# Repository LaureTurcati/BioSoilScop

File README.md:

# BioSoilScop
The VerY cool Cam Trap for soil ORganisms (VYCTOR)

This camera trap was designed to study ground fauna without disturbing or killing it.

VYCTOR consists of a waterproof sensor measuring approximately 25x25cm with removable and interchangeable 10cm feet. It is capable of taking images day and night thanks to a brightness detection device that activates a night vision mode with 8 infrared LEDs surrounding the camera. The system is controlled by a Raspberry Pi. The camera films continuously at low resolution (without recording) and an algorithm detects movement by comparing images in pairs (background subtraction + speed calculation + shape detection). When movement is detected, a series of high-definition photos is taken at regular intervals and stored. The device is powered by mains electricity or battery. A computer interface allows the measurement settings to be configured and the characteristics of the installation site to be entered. It has been designed to be easy to use by non-specialists.

<ins>Picture of the VYCTOR device </ins>  

 ## Examples of pictures taken
Here are some images taken during a laboratory test session.

<ins>Taken picture of a snail after motion detection</ins>

<ins>Motion detection representation</ins>

<ins>Speed detection representation</ins>

## Construction
Browse the hardware folder to construct your VYCTOR

## Documentation
Recover the documentation user and developpement in the Folder Software

## Credit
This project was funded by the French national research agency (ANR) BISES ANR-19-CE 32-0012, the OSU OREME and the OSU Ecce Terra

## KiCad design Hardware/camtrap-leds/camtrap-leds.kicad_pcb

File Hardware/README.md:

# CamTrap Hardware

Le CamTrap est organisé autour d'un Raspberry Pi.  
Il contient des parties imprimées en 3D et découpé au laser, cependant il est possible de faire sans.

## logiciels utilisés

Les PCBs ont été réalisés avec Kicad 7.0.
Les tracés laser avec Inkscape.

## Liste du Matériel

La liste du matériel se trouve dans le fichier "camtrap_bom.xlsx".

## Schéma de connection

## Liste des dossiers

Hardware  
├── camtrap/    
├── camtrap_usb_adapteur/  
├── camtrap3d/  
├── images/  
└── camtrap-leds/  

- **`camtrap`** : Contient les fichiers de fabrication de la carte head au dessus du Raspberry.  
- **`camtrap_usb_adapteur`** : Contient les fichiers de fabrication de la petite carte d'adaptation de la prise USB.  
- **`camtrap3d`** : Contient les fichiers d'impression et de découpe.  
- **`images`** : Contient les images pour le readme.  
- **`camtrap-leds`** :  Contient les fichiers de fabrication de la carte qui tient les leds

## Vue globale

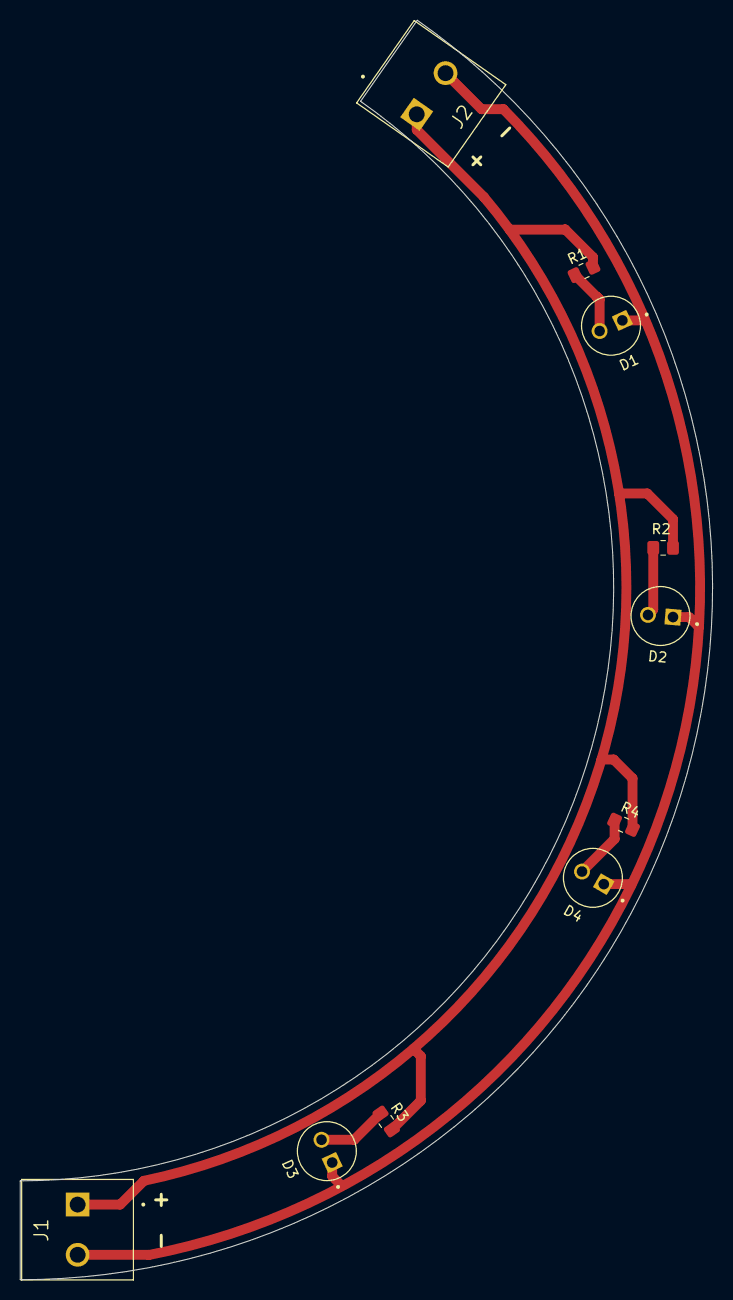
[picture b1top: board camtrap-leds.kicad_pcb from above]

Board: 2 copper layers, 70.0 x 127.3 mm, 10 parts (0 on the bottom side), 6 nets.

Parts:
D1, D2, D3, D4: TSHG6400; LEDRD254W55D595H900
J1, J2: TB010-508-02BE; CUI_TB010-508-02BE
R1, R2, R3, R4: R; R_0805_2012Metric_Pad1.20x1.40mm_HandSolder

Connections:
GND: D1.C, D2.C, D3.C, D4.C, J1.2, J2.2
unnamed: D1.A, R1.1
unnamed: D2.A, R2.1
unnamed: D3.A, R3.1
unnamed: D4.A, R4.1
unnamed: J1.1, J2.1, R1.2, R2.2, R3.2, R4.2

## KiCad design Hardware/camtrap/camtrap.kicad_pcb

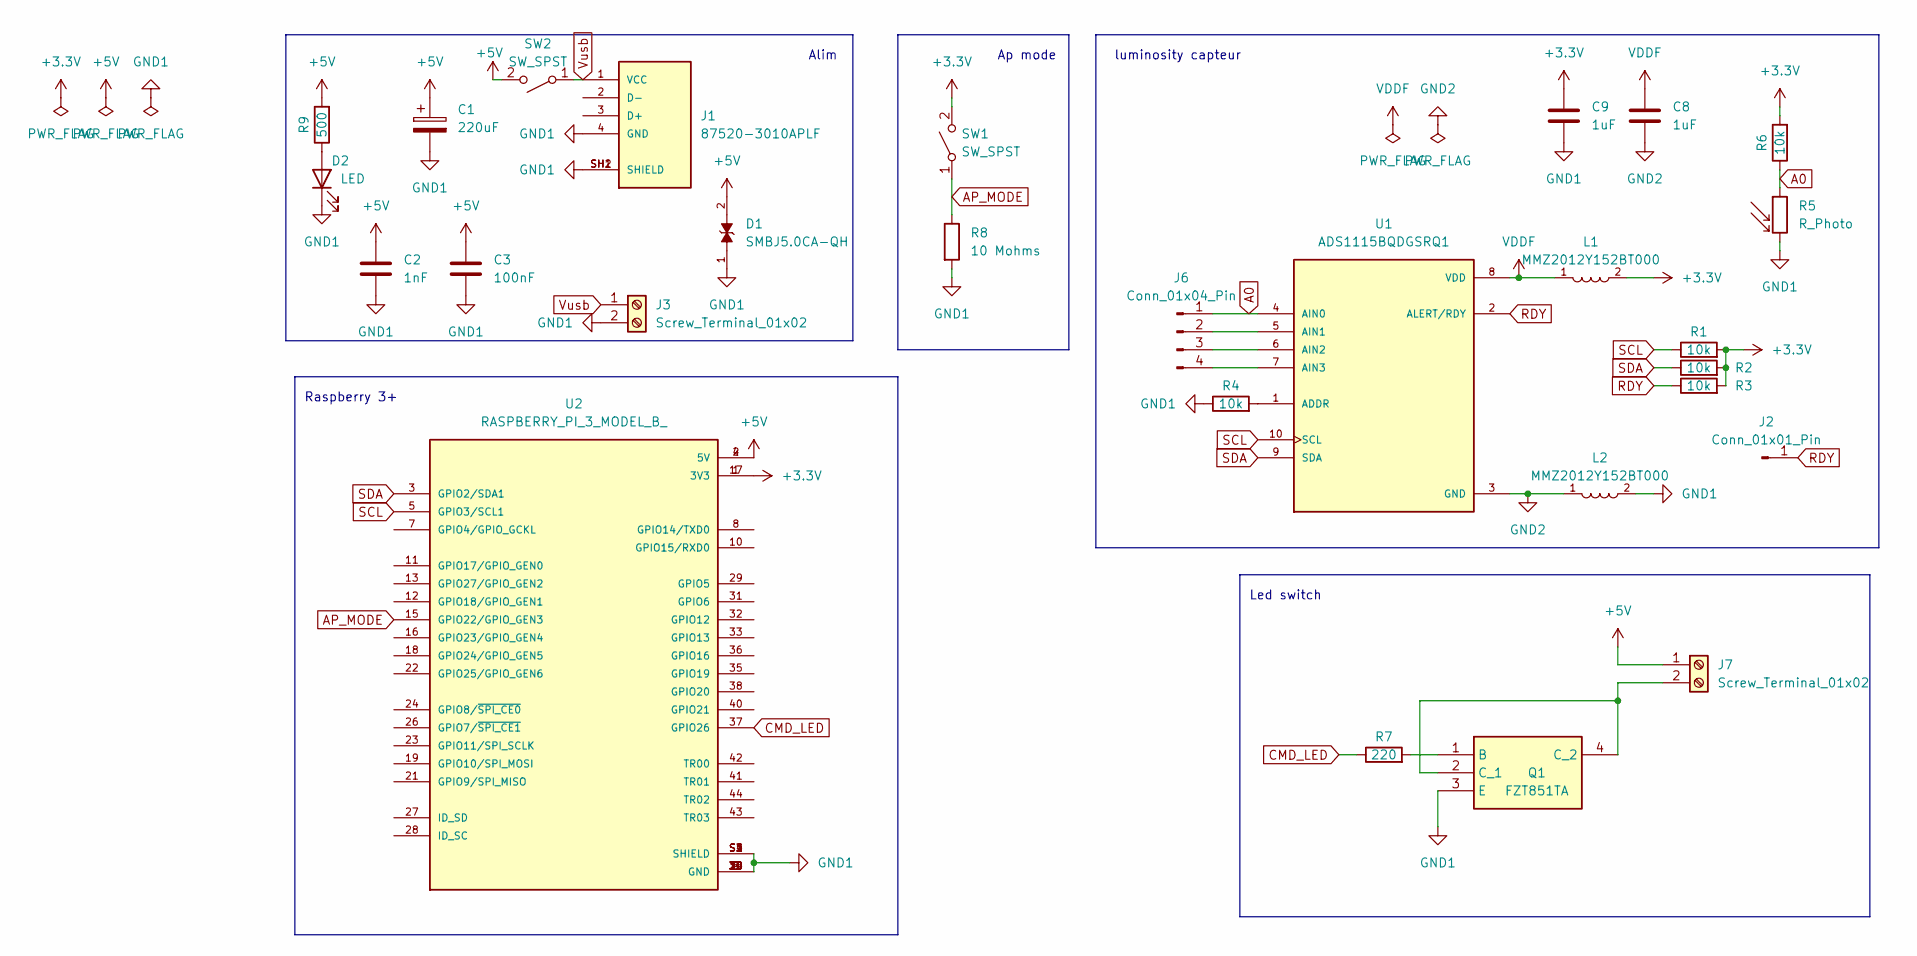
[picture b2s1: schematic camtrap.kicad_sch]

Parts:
C1: 220uF; CP_Radial_D8.0mm_P3.50mm
C2: 1nF; C_0805_2012Metric_Pad1.18x1.45mm_HandSolder
C3: 100nF; C_0805_2012Metric_Pad1.18x1.45mm_HandSolder
C8, C9: 1uF; C_0805_2012Metric_Pad1.18x1.45mm_HandSolder
D1: SMBJ5.0CA-QH; DIOM4336X265N; PARTREV I2102
D2: LED; PinHeader_1x02_P2.54mm_Vertical
J1: 87520-3010APLF; AMPHENOL_87520-3010APLF; PARTREV AR
J2: Conn_01x01_Pin; PinHeader_1x01_P2.54mm_Vertical
J3, J7: Screw_Terminal_01x02; bornierVis
J6: Conn_01x04_Pin; PinHeader_1x04_P2.54mm_Vertical
L1, L2: MMZ2012Y152BT000; INDC2012X87N
Q1: FZT851TA; SOT230P700X170-4N; Mouser Part Number 522-FZT851TA
R1, R2, R3, R4, R6: 10k; R_0805_2012Metric_Pad1.20x1.40mm_HandSolder
R5: R_Photo; PinHeader_1x02_P2.54mm_Vertical
R7: 220; R_0805_2012Metric_Pad1.20x1.40mm_HandSolder
R8: 10 Mohms; R_0805_2012Metric_Pad1.20x1.40mm_HandSolder
R9: 500; R_0805_2012Metric_Pad1.20x1.40mm_HandSolder
SW1, SW2: SW_SPST; PinHeader_1x02_P2.54mm_Vertical
U1: ADS1115BQDGSRQ1; SOP50P490X110-10N; PARTREV D
U2: RASPBERRY_PI_3_MODEL_B_; raspberrypi 3b+; PARTREV N/A

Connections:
+3.3V: C9.1, L1.2, R1.2, R2.2, R3.2, R6.2, SW1.2 (B), U2.1 (3V3), U2.17 (3V3)
+5V: C1.1, C2.1, C3.1, D1.2, J7.1, R9.2, SW2.2 (B), U2.2 (5V), U2.4 (5V)
A0: J6.1, R5.1, R6.1, U1.4 (AIN0)
AP_MODE: R8.1, SW1.1 (A), U2.15 (GPIO22/GPIO_GEN3)
CMD_LED: R7.1, U2.37 (GPIO26)
GND1: C1.2, C2.2, C3.2, C9.2, D1.1, D2.1 (K), J1.4 (GND), J1.SH1 (SHIELD), J1.SH2 (SHIELD), J3.2, L2.2, Q1.3 (E), R4.1, R5.2, R8.2, U2.6 (GND), U2.9 (GND), U2.14 (GND), U2.20 (GND), U2.25 (GND), U2.30 (GND), U2.34 (GND), U2.39 (GND), U2.S1 (SHIELD), U2.S2 (SHIELD), U2.S3 (SHIELD), U2.S4 (SHIELD)
GND2: C8.2, L2.1, U1.3 (GND)
unnamed: D2.2 (A), R9.1
unnamed: J6.2, U1.5 (AIN1)
unnamed: J6.3, U1.6 (AIN2)
unnamed: J6.4, U1.7 (AIN3)
unnamed: J7.2, Q1.2 (C_1), Q1.4 (C_2)
unnamed: Q1.1 (B), R7.2
unnamed: R4.2, U1.1 (ADDR)
RDY: J2.1, R3.1, U1.2 (ALERT/RDY)
SCL: R1.1, U1.10 (SCL), U2.5 (GPIO3/SCL1)
SDA: R2.1, U1.9 (SDA), U2.3 (GPIO2/SDA1)
VDDF: C8.1, L1.1, U1.8 (VDD)
Vusb: J1.1 (VCC), J3.1, SW2.1 (A)

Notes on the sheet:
Ap mode
luminosity capteur
Raspberry 3+
Led switch
Alim

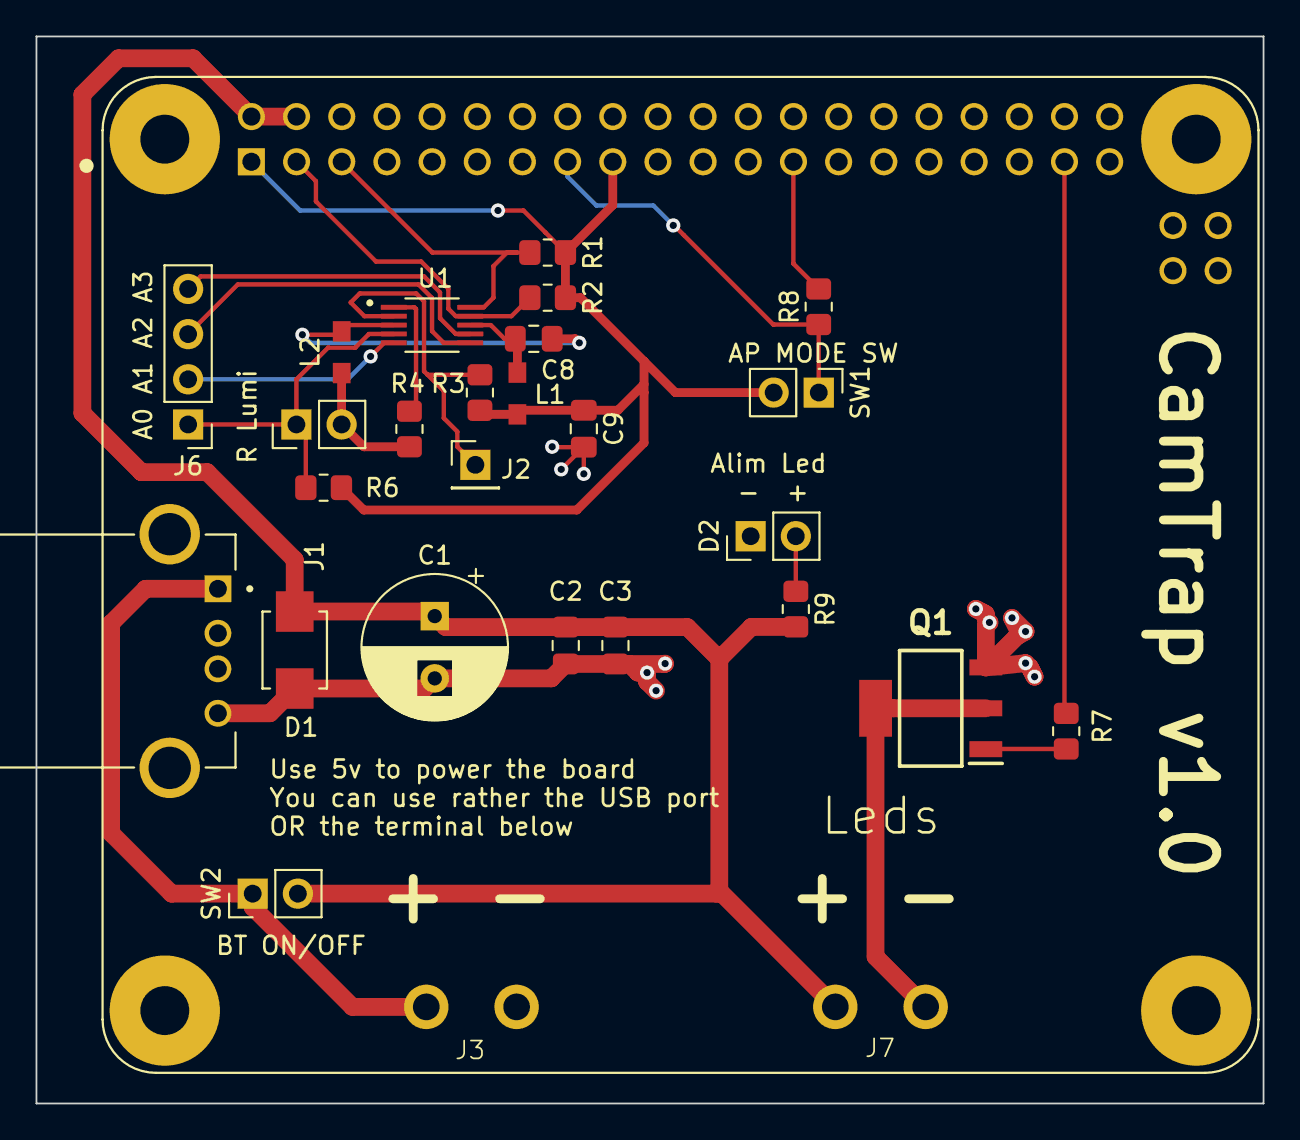
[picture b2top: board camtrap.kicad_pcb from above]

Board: 2 copper layers, 69.0 x 60.0 mm, 28 parts (0 on the bottom side), 19 nets.

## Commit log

2025-12-19 recover old repo
2025-12-19 adding pictures
2026-01-26 add new base
